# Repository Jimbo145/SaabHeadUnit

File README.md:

# SaabHeadUnit
The goal of this project is to create an alternate head unit option for the 
## saab-control

## circuit_boards

### headunit_controls

Emulates slimmed down ICM button pcb

### headunit_hub

Integrates Ibus and LCD connections to Cat V cables for routing out of ICM

### headunit_pi4

Pi4 mounting, Lifepowered, Microphone module, power input

# Project Phases

## Phase 1 -- ICM2 Integration

Parts list
[Raspberry Pi LCD 3.5inch touchscreen 480*800 capacitive](https://www.aliexpress.us/item/3256802078662650.html)
[lifepo4wered-pi+](https://lifepo4wered.com/lifepo4wered-pi+.html)
[Can Bus Module Mcp2515](https://www.aliexpress.us/item/3256802493611620.html)

## Phase 2 -- ICM Frontend Replacement

# Acknowledgement 

[leighleighleigh](https://github.com/leighleighleigh)
[Patrick Van Oosterwijck and LiFePO4wered](https://lifepo4wered.com)
[Trionic Tuning](https://www.trionictuning.com/forum/viewtopic.php?f=46&t=8566)

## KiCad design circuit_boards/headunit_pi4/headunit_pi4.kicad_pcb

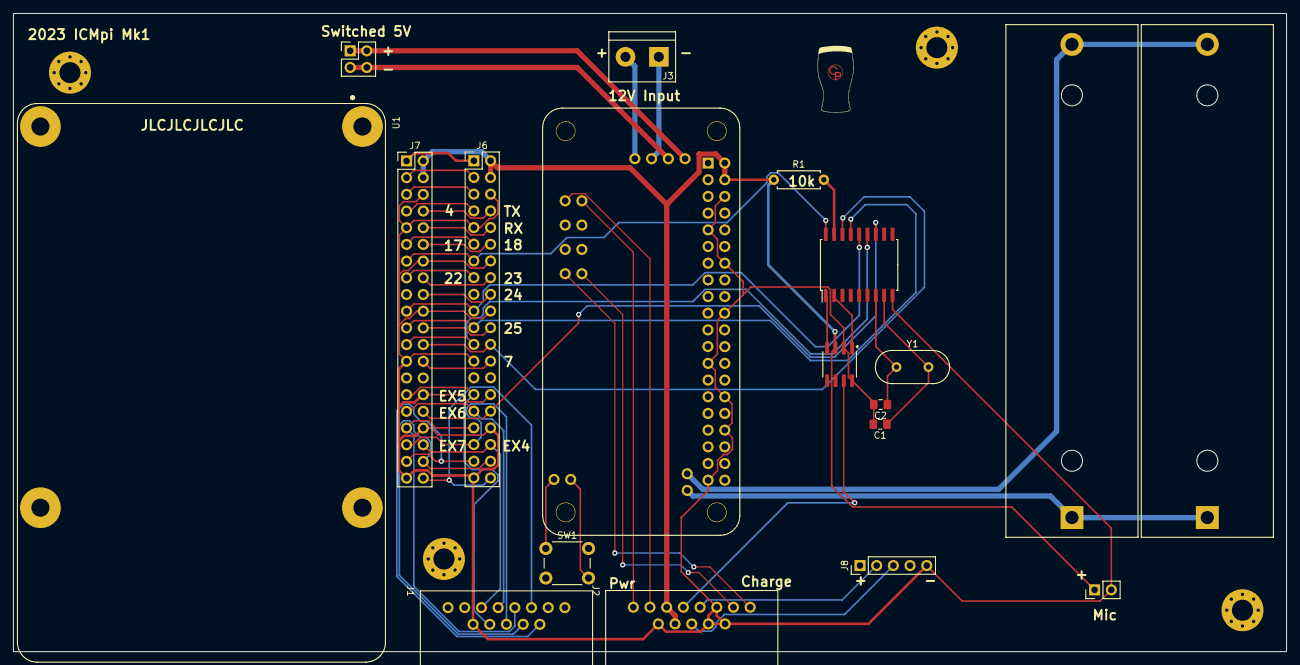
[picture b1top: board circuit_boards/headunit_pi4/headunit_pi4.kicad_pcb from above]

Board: 2 copper layers, 193.7 x 97.1 mm, 24 parts (0 on the bottom side), 50 nets.

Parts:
BT1, BT2: Battery_Cell; BatteryHolder_MPD_BH-18650-PC2
C1, C2: 22p; C_0805_2012Metric_Pad1.18x1.45mm_HandSolder
H1, H2, H3, H4: MountingHole_Pad; MountingHole_3.2mm_M3_Pad_Via
H5: MountingHole; CPlogo2(50)
J1, J2: 8P8C_LED_Shielded; rj45breakout
J3: Screw_Terminal_01x02; TerminalBlock_bornier-2_P5.08mm
J4: Conn_01x02; PinHeader_1x02_P2.54mm_Vertical
J5: Conn_02x02_Counter_Clockwise; PinHeader_2x02_P2.54mm_Vertical
J6, J7: Conn_02x20_Odd_Even; PinHeader_2x20_P2.54mm_Vertical
J8: USB_B_Mini; PinHeader_1x05_P2.54mm_Vertical
R1: 10k; R_Axial_DIN0207_L6.3mm_D2.5mm_P7.62mm_Horizontal
SW1: SW_Push; SW_PUSH_6mm
U1: RASPBERRY_PI_4B_4GB; MODULE_RASPBERRY_PI_4B_4GB_NOPIN
U2: TJA1051T; SOIC-8_3.9x4.9mm_P1.27mm
U3: MCP2515-xSO; SOIC-18W_7.5x11.6mm_P1.27mm
U4: LiFoPower
Y1: 8Mhz; Crystal_HC49-U_Vertical

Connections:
+3.3V: J6.1, J7.1
AMFM_button: J1.1, J6.37, J7.37
CAN_INT: J6.32, J7.32, U3.12 (~INT)
CD_button: J1.3, J6.38, J7.38
ChargeLED+: J2.10, U4.Cled+ (ChargeLED+)
ChargeLED-: J2.9, U4.Cled- (ChargeLED-)
Expansion_4: J1.8, J6.36, J7.36
Expansion_5: J1.7, J6.29, J7.29
Expansion_6: J1.6, J6.31, J7.31
Expansion_7: J1.5, J6.35, J7.35
GND: C1.2, C2.2, H1.1, H2.1, H3.1, H4.1, J1.SH, J2.1, J2.2, J2.3, J2.SH, J4.2, J6.6, J6.9, J6.14, J6.20, J6.25, J6.30, J6.34, J6.39, J7.6, J7.9, J7.14, J7.20, J7.25, J7.30, J7.34, J7.39, J8.5 (GND), U2.2 (GND), U2.8 (S), U3.9 (VSS), U4.6 (GND), U4.9 (GND), U4.14 (GND), U4.20 (GND), U4.25 (GND), U4.30 (GND), U4.34 (GND), U4.39 (GND)
GPIO4: J6.7, J7.7
GPIO7: J6.26, J7.26
GPIO17: J6.11, J7.11
GPIO18: J6.12, J7.12
GPIO22: J6.15, J7.15
GPIO23: J6.16, J7.16
GPIO24: J6.18, J7.18
GPIO25: J6.22, J7.22
LSCAN: J2.6, U2.7 (CANH)
MCP_PWR: J6.13, J7.13, U3.18 (VDD)
unnamed: BT1.1 (+), BT2.1 (+), U4.B+ (Bat+)
unnamed: BT1.2 (-), BT2.2 (-), U4.B- (Bat-)
unnamed: J3.1, U4.Vcar- (12VGND)
unnamed: J3.2, U4.Vcar+ (12V+)
unnamed: J5.1, J5.2, U4.Vout+
unnamed: J5.3, J5.4, U4.Vout-
unnamed: J2.5, J8.3 (D+)
unnamed: J2.4, J8.2 (D-)
unnamed: U1.S1 (SHIELD), U1.S2 (SHIELD), U1.S3 (SHIELD), U1.S4 (SHIELD)
unnamed: U2.4 (RXD), U3.2 (RXCAN)
unnamed: U2.1 (TXD), U3.1 (TXCAN)
unnamed: C1.1, U3.8 (OSC1), Y1.2
unnamed: C2.1, U3.7 (OSC2), Y1.1
unnamed: R1.2, U3.17 (~RESET)
unnamed: SW1.2, U4.btn+ (BTN+)
unnamed: SW1.1, U4.btn- (BTN-)
PwrLED+: J2.12, U4.Pled+ (PowerLED+)
PwrLED-: J2.11, U4.Pled- (PowerLED-)
RX0: J6.10, J7.10
SCAN_button: J1.2, J6.40, J7.40
SCL1: J6.5, J7.5, U4.5 (SCL)
SDA1: J6.3, J7.3, U4.3 (SDA)
SPI0_CE0: J6.24, J7.24, U3.16 (~CS)
SPI0_MISO: J6.21, J7.21, U3.15 (SO)
SPI0_MOSI: J6.19, J7.19, U3.14 (SI)
SPI0_SCLK: J6.23, J7.23, U3.13 (SCK)
Scrn_Brightness: J1.4, J6.33, J7.33
TX0: J6.8, J7.8, U4.8 (TX0)
VCC: J2.7, J2.8, J4.1, J6.2, J6.4, J7.2, J7.4, R1.1, U2.3 (VCC), U4.2 (VCC), U4.4 (VCC)

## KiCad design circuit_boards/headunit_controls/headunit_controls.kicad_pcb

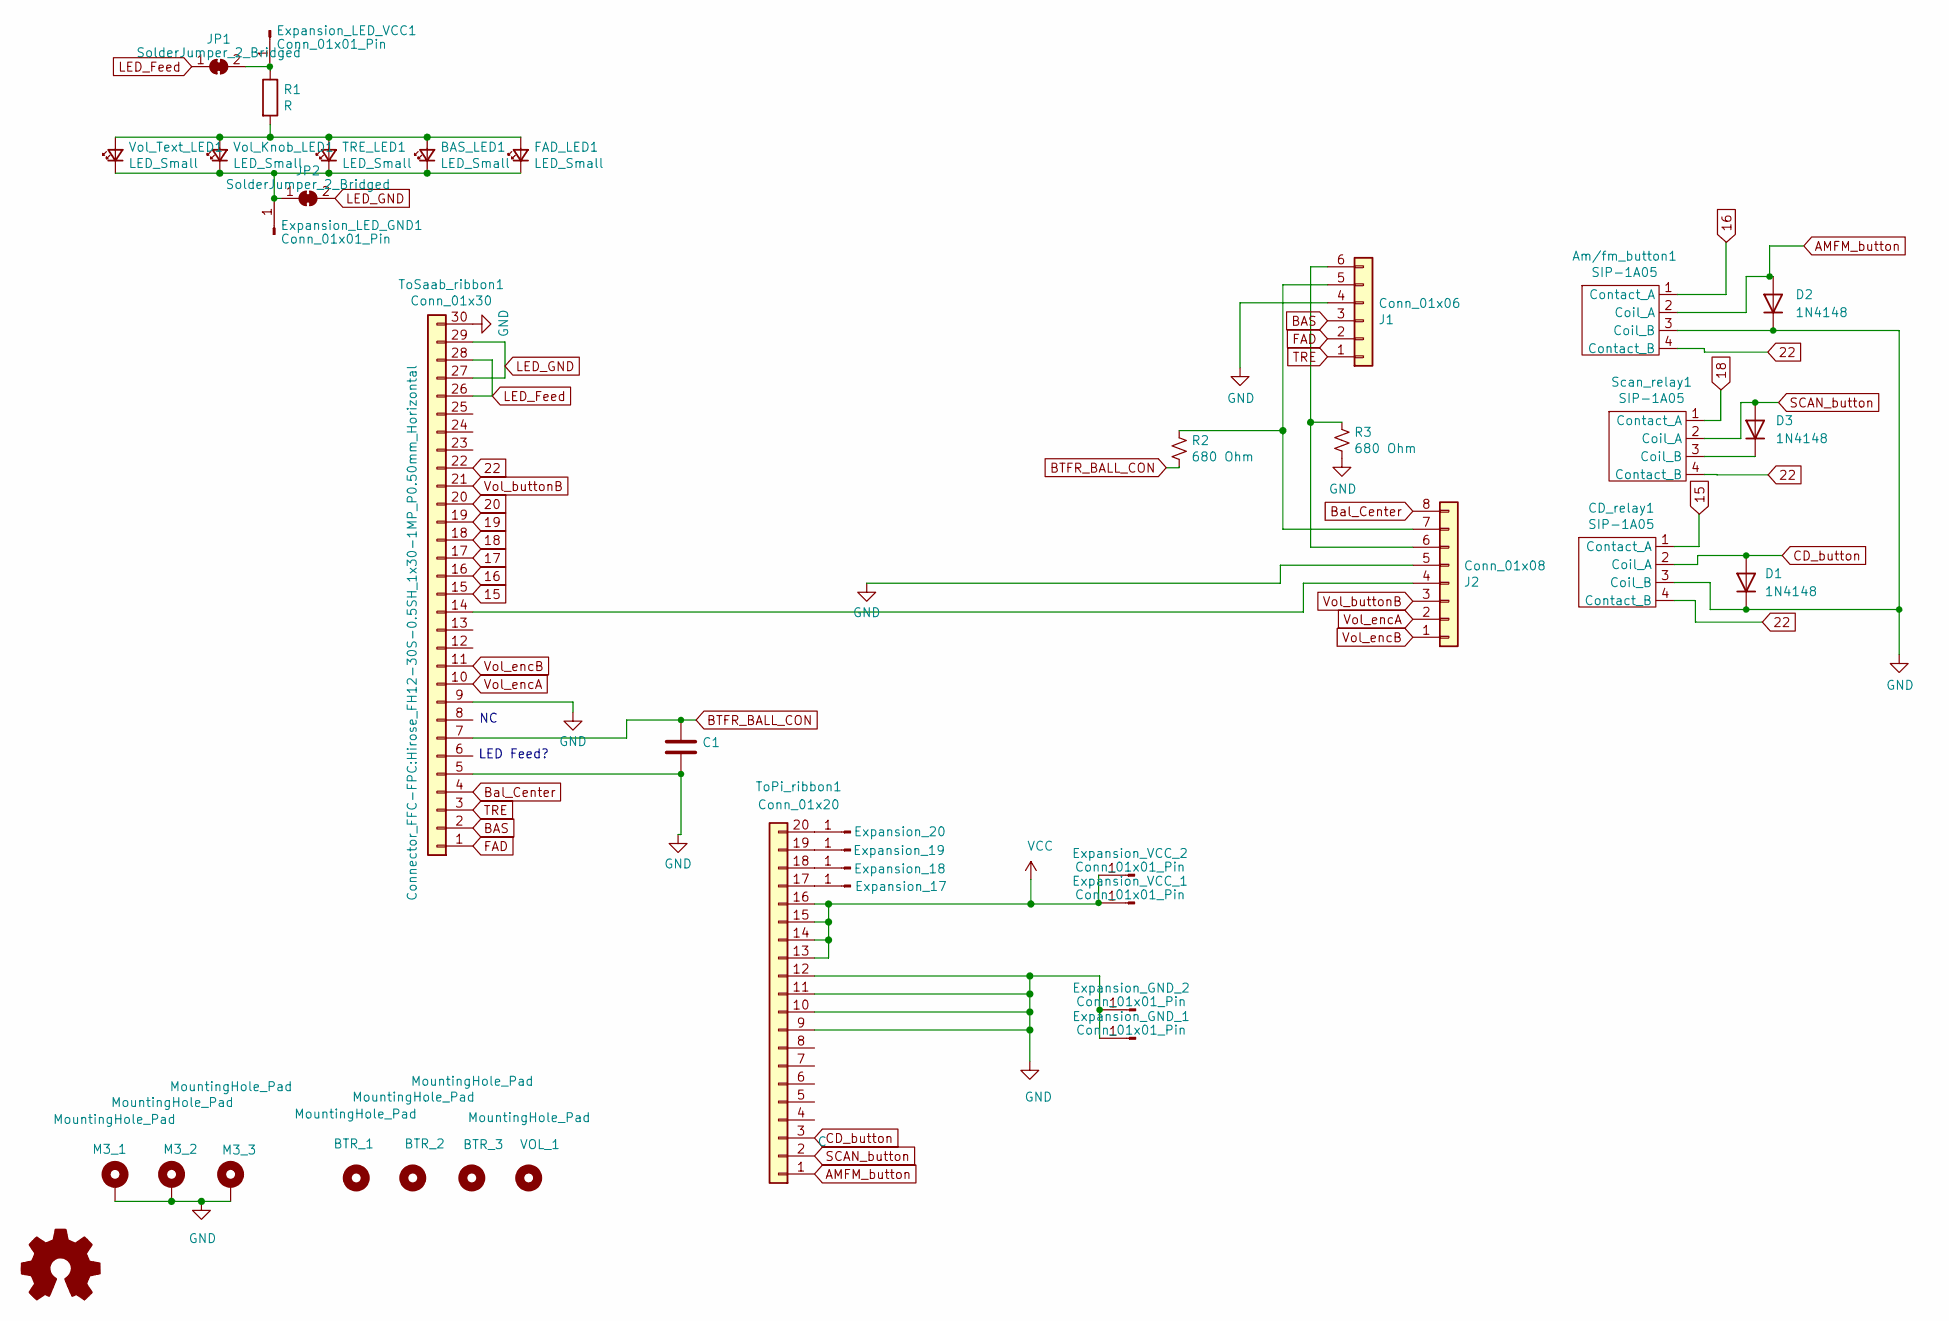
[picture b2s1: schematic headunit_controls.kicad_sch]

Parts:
Am/fm_button1: SIP-1A05; SIP1A05
BAS_LED1: LED_Small; LED_OF-SMD3528WC
BTR_1, BTR_2, BTR_3: MountingHole_Pad; SaabBTR
C1: C; C_0805_2012Metric_Pad1.18x1.45mm_HandSolder
CD_relay1: SIP-1A05; SIP1A05
D1, D2, D3: 1N4148; D_DO-35_SOD27_P7.62mm_Horizontal
Expansion_17, Expansion_18, Expansion_19, Expansion_20: Conn_01x01_Pin; TestPoint_Pad_2.0x2.0mm
Expansion_GND_1, Expansion_GND_2: Conn_01x01_Pin; TestPoint_Pad_2.0x2.0mm
Expansion_LED_GND1: Conn_01x01_Pin; TestPoint_Pad_2.0x2.0mm
Expansion_LED_VCC1: Conn_01x01_Pin; TestPoint_Pad_2.0x2.0mm
Expansion_VCC_1, Expansion_VCC_2: Conn_01x01_Pin; TestPoint_Pad_2.0x2.0mm
FAD_LED1: LED_Small; LED_OF-SMD3528WC
J1: Conn_01x06; SaabConnector_6
J2: Conn_01x08; SaabConnector_8
JP1, JP2: SolderJumper_2_Bridged; SolderJumper-2_P1.3mm_Bridged2Bar_Pad1.0x1.5mm
M3_1, M3_2, M3_3: MountingHole_Pad; MountingHole_3.2mm_M3_Pad
R1: R; R_0603_1608Metric_Pad0.98x0.95mm_HandSolder
R2, R3: 680 Ohm; R_0603_1608Metric_Pad0.98x0.95mm_HandSolder
Scan_relay1: SIP-1A05; SIP1A05
TRE_LED1: LED_Small; LED_OF-SMD3528WC
ToPi_ribbon1: Conn_01x20; Hirose_FH12-20S-0.5SH_1x20-1MP_P0.50mm_Horizontal
ToSaab_ribbon1: Conn_01x30; Hirose_FH12-30S-0.5SH_1x30-1MP_P0.50mm_Horizontal
VOL_1: MountingHole_Pad; SaabBTR
Vol_Knob_LED1: LED_Small; Songxin_1210_side
Vol_Text_LED1: LED_Small; LED_OF-SMD3528WC

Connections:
15: CD_relay1.1 (Contact_A), ToSaab_ribbon1.15
16: Am/fm_button1.1 (Contact_A), ToSaab_ribbon1.16
17: ToSaab_ribbon1.17
18: Scan_relay1.1 (Contact_A), ToSaab_ribbon1.18
19: ToSaab_ribbon1.19
20: ToSaab_ribbon1.20
22: Am/fm_button1.4 (Contact_B), CD_relay1.4 (Contact_B), Scan_relay1.4 (Contact_B), ToSaab_ribbon1.22
AMFM_button: Am/fm_button1.2 (Coil_A), D2.2 (A), ToPi_ribbon1.1
BAS: J1.3, ToSaab_ribbon1.2
BTFR_BALL_CON: C1.1, R2.2, ToSaab_ribbon1.7
Bal_Center: J2.8, ToSaab_ribbon1.4
CD_button: CD_relay1.2 (Coil_A), D1.2 (A), ToPi_ribbon1.3
FAD: J1.2, ToSaab_ribbon1.1
GND: Am/fm_button1.3 (Coil_B), C1.2, CD_relay1.3 (Coil_B), D1.1 (K), D2.1 (K), Expansion_GND_1.1, Expansion_GND_2.1, J1.4, J2.5, M3_1.1, M3_2.1, M3_3.1, R3.2, ToPi_ribbon1.9, ToPi_ribbon1.10, ToPi_ribbon1.11, ToPi_ribbon1.12, ToSaab_ribbon1.5, ToSaab_ribbon1.9, ToSaab_ribbon1.30; also elsewhere on the board
LED_Feed: JP1.1 (A), ToSaab_ribbon1.26, ToSaab_ribbon1.28
LED_GND: JP2.2 (B), ToSaab_ribbon1.27, ToSaab_ribbon1.29
unnamed: BAS_LED1.2 (A), FAD_LED1.2 (A), R1.2, TRE_LED1.2 (A), Vol_Knob_LED1.2 (A), Vol_Text_LED1.2 (A)
unnamed: BAS_LED1.1 (K), Expansion_LED_GND1.1, FAD_LED1.1 (K), JP2.1 (A), TRE_LED1.1 (K), Vol_Knob_LED1.1 (K), Vol_Text_LED1.1 (K)
unnamed: D3.1 (K), Scan_relay1.3 (Coil_B)
unnamed: Expansion_17.1, ToPi_ribbon1.17
unnamed: Expansion_18.1, ToPi_ribbon1.18
unnamed: Expansion_19.1, ToPi_ribbon1.19
unnamed: Expansion_20.1, ToPi_ribbon1.20
unnamed: Expansion_LED_VCC1.1, JP1.2 (B), R1.1
unnamed: J1.5, J2.7, R2.1
unnamed: J1.6, J2.6, R3.1
unnamed: J2.4, ToSaab_ribbon1.14
SCAN_button: D3.2 (A), Scan_relay1.2 (Coil_A), ToPi_ribbon1.2
TRE: J1.1, ToSaab_ribbon1.3
VCC: Expansion_VCC_1.1, Expansion_VCC_2.1, ToPi_ribbon1.13, ToPi_ribbon1.14, ToPi_ribbon1.15, ToPi_ribbon1.16
Vol_buttonB: J2.3, ToSaab_ribbon1.21
Vol_encA: J2.2, ToSaab_ribbon1.10
Vol_encB: J2.1, ToSaab_ribbon1.11

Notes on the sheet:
LED Feed?

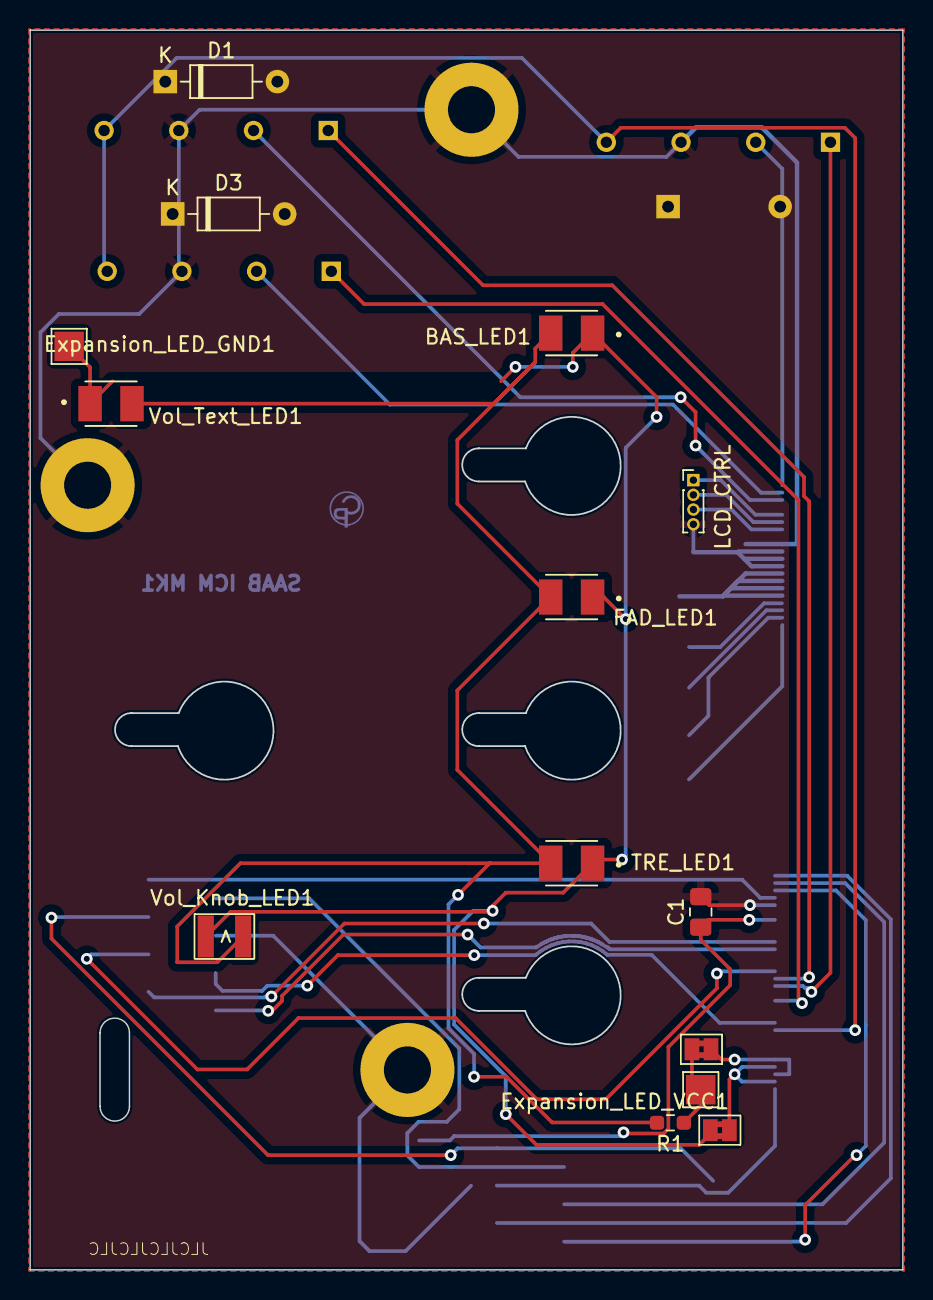
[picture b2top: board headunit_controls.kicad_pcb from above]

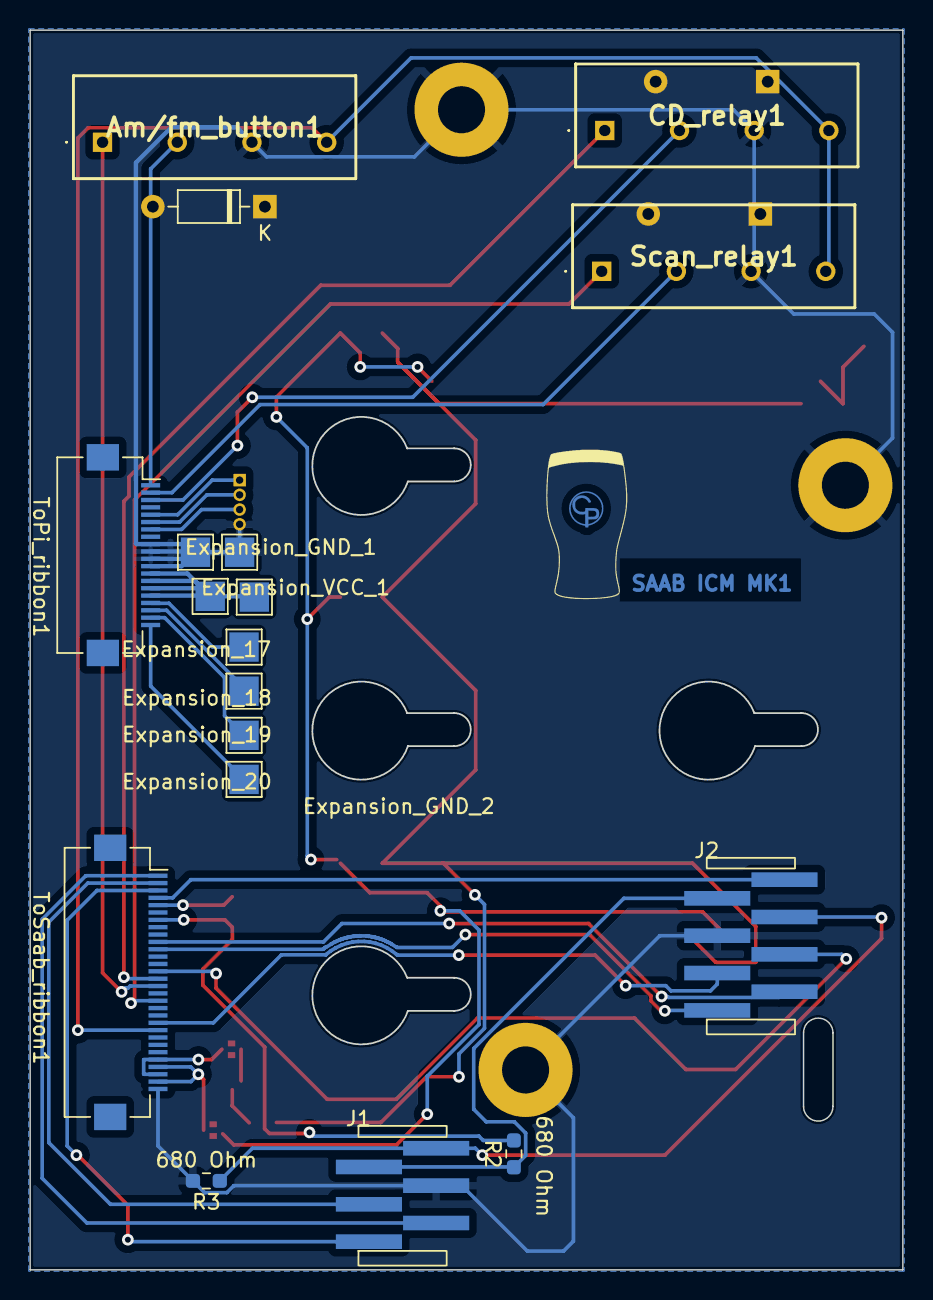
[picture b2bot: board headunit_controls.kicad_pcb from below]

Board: 2 copper layers, 59.3 x 84.3 mm, 40 parts (19 on the bottom side), 30 nets.

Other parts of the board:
LCD_CTRL: Conn_01x04_Pin; PinHeader_1x04_P1.00mm_Vertical
Ref**: Val**; CPlogo2(50)

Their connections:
GND: LCD_CTRL.4; also elsewhere on the board

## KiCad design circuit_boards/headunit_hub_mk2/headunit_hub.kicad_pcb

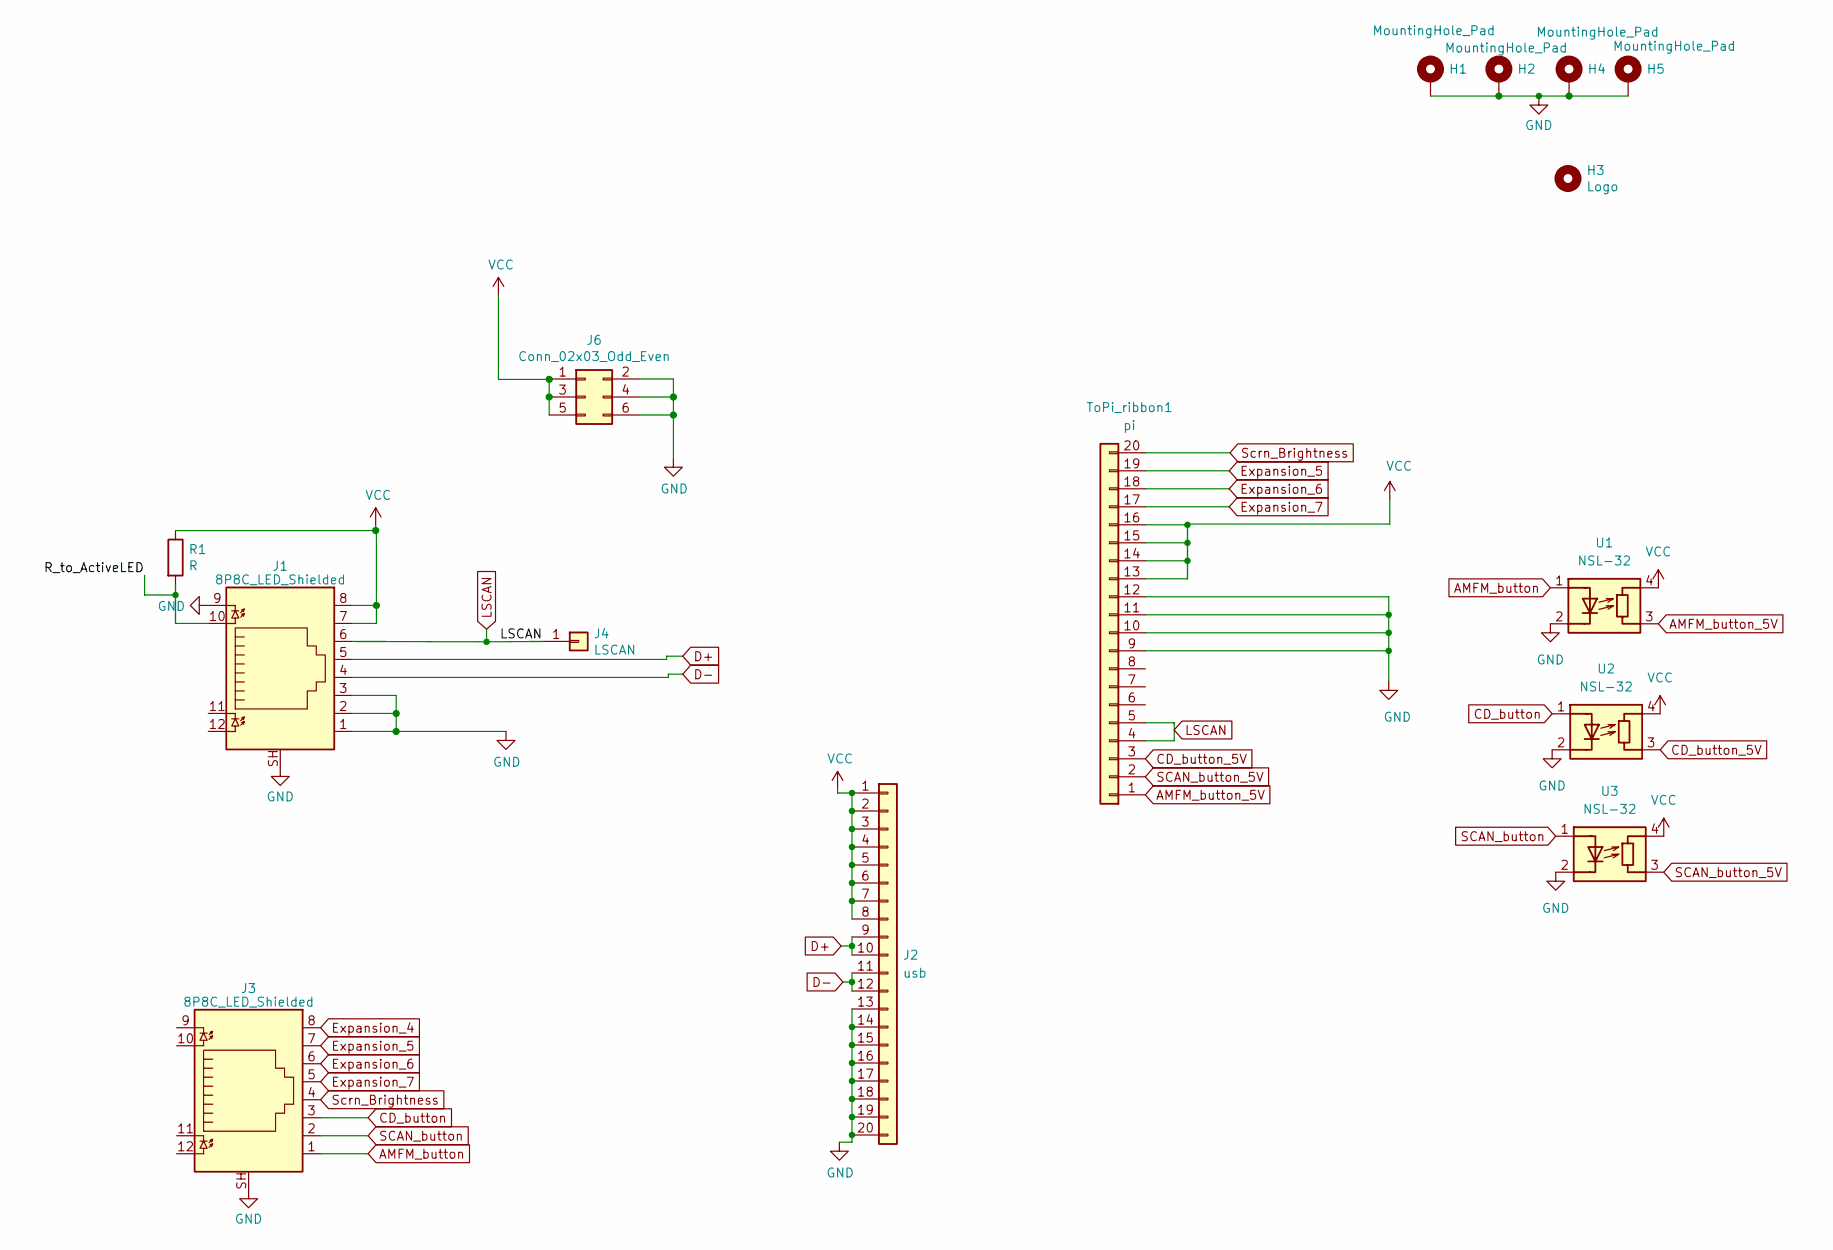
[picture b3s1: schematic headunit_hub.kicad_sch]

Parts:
H1, H2, H4, H5: MountingHole_Pad; MountingHole_3.2mm_M3_Pad_Via
H3: Logo; CPlogo2(50)
J1, J3: 8P8C_LED_Shielded; RJ45_Amphenol_RJHSE538X
J2: usb; Hirose_FH12-20S-0.5SH_1x20-1MP_P0.50mm_Horizontal
J4: LSCAN; PinHeader_1x01_P2.54mm_Vertical
J6: Conn_02x03_Odd_Even; PinHeader_2x03_P2.54mm_Vertical
R1: R; R_Axial_DIN0207_L6.3mm_D2.5mm_P10.16mm_Horizontal
ToPi_ribbon1: pi; Hirose_FH12-20S-0.5SH_1x20-1MP_P0.50mm_Horizontal
U1, U2, U3: NSL-32; Luna_NSL-32

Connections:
/R_to_ActiveLED: J1.10, R1.2
AMFM_button: J3.1, U1.1 (A)
AMFM_button_5V: ToPi_ribbon1.1, U1.3 (R)
CD_button: J3.3, U2.1 (A)
CD_button_5V: ToPi_ribbon1.3, U2.3 (R)
D+: J1.5, J2.9, J2.10
D-: J1.4, J2.11, J2.12
Expansion_4: J3.8
Expansion_5: J3.7, ToPi_ribbon1.19
Expansion_6: J3.6, ToPi_ribbon1.18
Expansion_7: J3.5, ToPi_ribbon1.17
GND: H1.1, H2.1, H4.1, H5.1, J1.1, J1.2, J1.3, J1.9, J1.SH, J2.13, J2.14, J2.15, J2.16, J2.17, J2.18, J2.19, J2.20, J3.SH, J6.2, J6.4, J6.6, ToPi_ribbon1.9, ToPi_ribbon1.10, ToPi_ribbon1.11, ToPi_ribbon1.12, U1.2 (K), U2.2 (K), U3.2 (K)
LSCAN: J1.6, J4.1, ToPi_ribbon1.4, ToPi_ribbon1.5
SCAN_button: J3.2, U3.1 (A)
SCAN_button_5V: ToPi_ribbon1.2, U3.3 (R)
Scrn_Brightness: J3.4, ToPi_ribbon1.20
VCC: J1.7, J1.8, J2.1, J2.2, J2.3, J2.4, J2.5, J2.6, J2.7, J2.8, J6.1, J6.3, J6.5, R1.1, ToPi_ribbon1.13, ToPi_ribbon1.14, ToPi_ribbon1.15, ToPi_ribbon1.16, U1.4 (R), U2.4 (R), U3.4 (R)

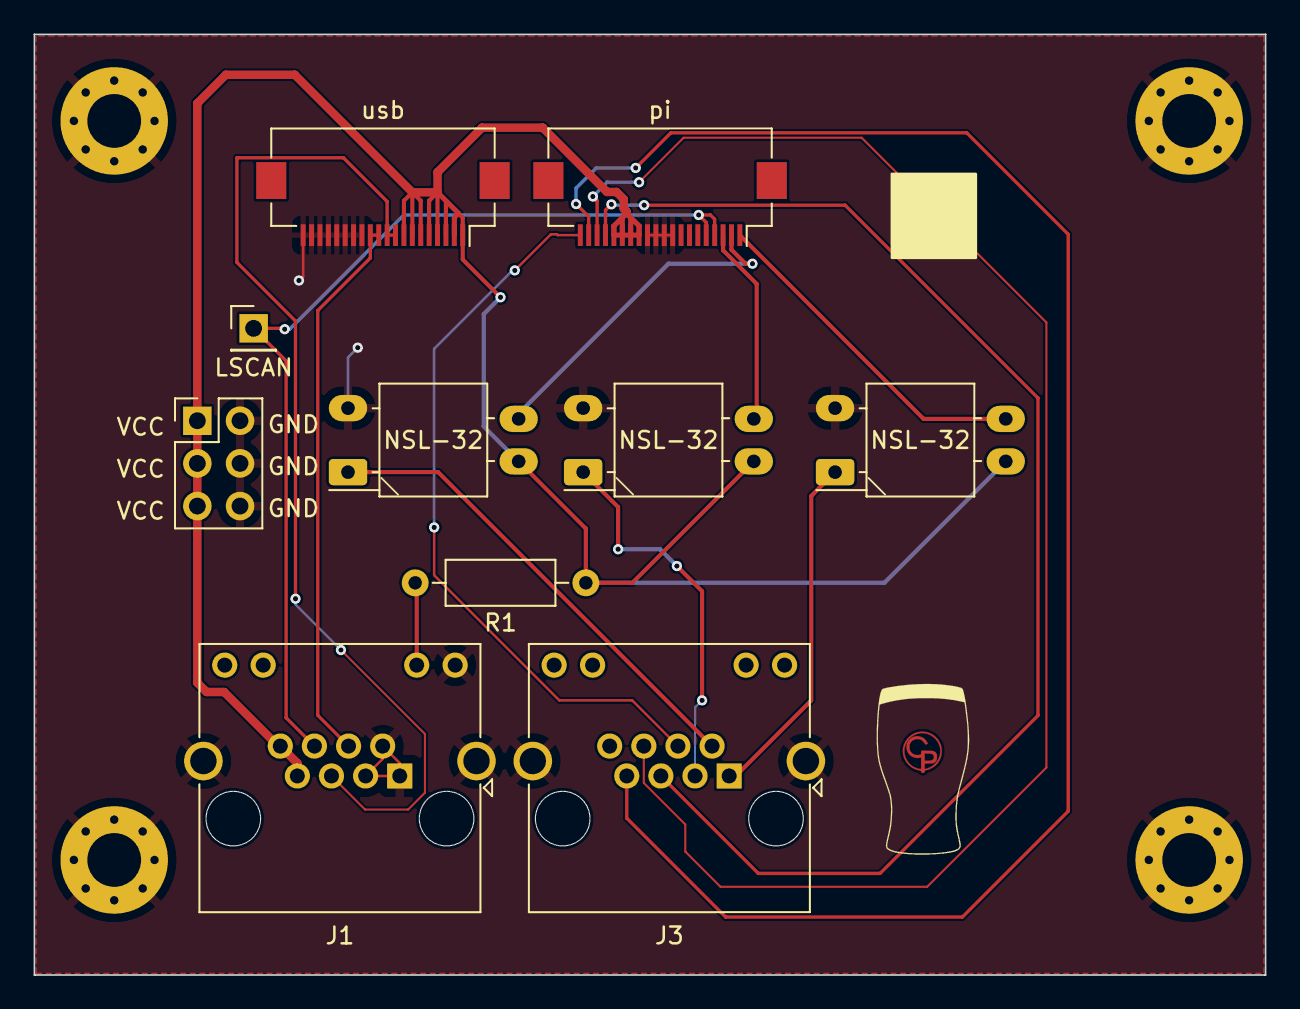
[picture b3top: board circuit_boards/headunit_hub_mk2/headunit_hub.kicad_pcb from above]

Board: 2 copper layers, 73.3 x 56.0 mm, 15 parts (0 on the bottom side), 16 nets.

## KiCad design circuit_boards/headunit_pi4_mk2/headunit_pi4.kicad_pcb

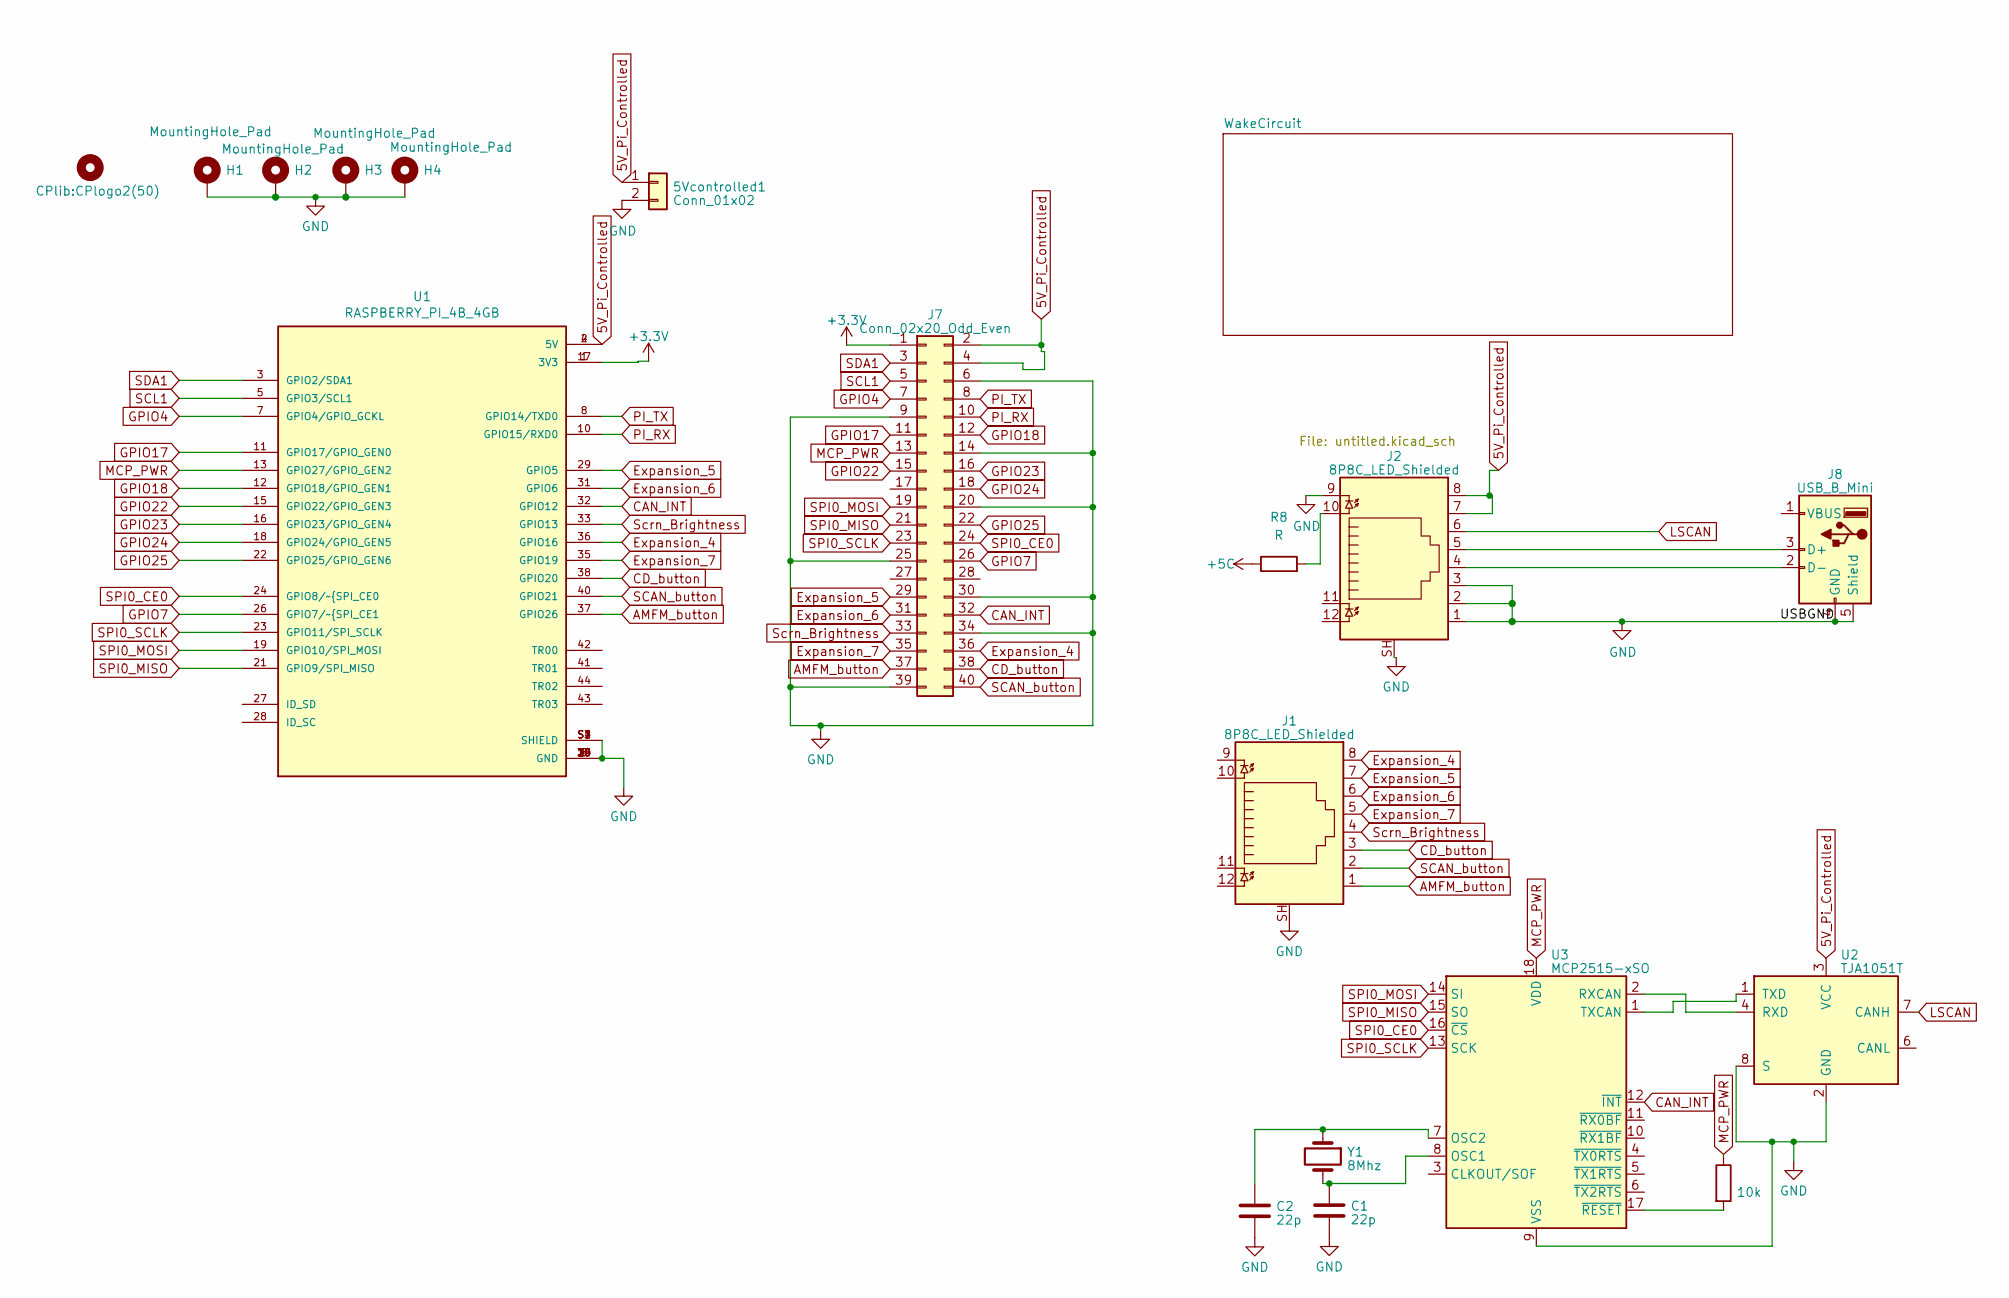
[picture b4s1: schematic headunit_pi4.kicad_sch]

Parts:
5Vcontrolled1: Conn_01x02; PinHeader_1x02_P2.54mm_Vertical
C1, C2: 22p; C_0805_2012Metric_Pad1.18x1.45mm_HandSolder
H1, H2, H3, H4: MountingHole_Pad; MountingHole_3.2mm_M3_Pad_Via
H5: MountingHole; CPlogo2(50)
J1, J2: 8P8C_LED_Shielded; RJ45_Amphenol_RJHSE538X
J7: Conn_02x20_Odd_Even; PinHeader_2x20_P2.54mm_Vertical
J8: USB_B_Mini; USB_A_Molex_67643_Horizontal
R1: 10k; R_Axial_DIN0207_L6.3mm_D2.5mm_P10.16mm_Horizontal
R8: R; R_Axial_DIN0207_L6.3mm_D2.5mm_P10.16mm_Horizontal
U1: RASPBERRY_PI_4B_4GB; MODULE_RASPBERRY_PI_4B_4GB; PARTREV 4
U2: TJA1051T; SOIC-8_3.9x4.9mm_P1.27mm
U3: MCP2515-xSO; SOIC-18W_7.5x11.6mm_P1.27mm
Y1: 8Mhz; Crystal_HC49-U_Vertical

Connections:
5V_Pi_Controlled: 5Vcontrolled1.1, J2.7, J2.8, J7.2, J7.4, U1.2 (5V), U1.4 (5V), U2.3 (VCC); also elsewhere on the board
+3.3V: J7.1, U1.1 (3V3), U1.17 (3V3)
+5C: R8.1; also elsewhere on the board
AMFM_button: J1.1, J7.37, U1.37 (GPIO26)
CAN_INT: J7.32, U1.32 (GPIO12), U3.12 (~INT)
CD_button: J1.3, J7.38, U1.38 (GPIO20)
Expansion_4: J1.8, J7.36, U1.36 (GPIO16)
Expansion_5: J1.7, J7.29, U1.29 (GPIO5)
Expansion_6: J1.6, J7.31, U1.31 (GPIO6)
Expansion_7: J1.5, J7.35, U1.35 (GPIO19)
GND: 5Vcontrolled1.2, C1.2, C2.2, H1.1, H2.1, H3.1, H4.1, J1.SH, J2.1, J2.2, J2.3, J2.9, J2.SH, J7.6, J7.9, J7.14, J7.20, J7.25, J7.30, J7.34, J7.39, J8.4 (GND), J8.5 (Shield), U1.6 (GND), U1.9 (GND), U1.14 (GND), U1.20 (GND), U1.25 (GND), U1.30 (GND), U1.34 (GND), U1.39 (GND), U1.S1 (SHIELD), U1.S2 (SHIELD), U1.S3 (SHIELD), U1.S4 (SHIELD), U2.2 (GND), U2.8 (S), U3.9 (VSS); also elsewhere on the board
GPIO4: J7.7, U1.7 (GPIO4/GPIO_GCKL)
GPIO7: J7.26, U1.26 (GPIO7/~SPI_CE1~{)
GPIO17: J7.11, U1.11 (GPIO17/GPIO_GEN0)
GPIO18: J7.12, U1.12 (GPIO18/GPIO_GEN1)
GPIO22: J7.15, U1.15 (GPIO22/GPIO_GEN3)
GPIO23: J7.16, U1.16 (GPIO23/GPIO_GEN4)
GPIO24: J7.18, U1.18 (GPIO24/GPIO_GEN5)
GPIO25: J7.22, U1.22 (GPIO25/GPIO_GEN6)
LSCAN: J2.6, U2.7 (CANH); also elsewhere on the board
MCP_PWR: J7.13, R1.1, U1.13 (GPIO27/GPIO_GEN2), U3.18 (VDD)
unnamed: J2.10, R8.2
unnamed: J2.5, J8.3 (D+)
unnamed: J2.4, J8.2 (D-)
unnamed: U2.4 (RXD), U3.2 (RXCAN)
unnamed: U2.1 (TXD), U3.1 (TXCAN)
unnamed: C1.1, U3.8 (OSC1), Y1.2
unnamed: C2.1, U3.7 (OSC2), Y1.1
unnamed: R1.2, U3.17 (~RESET)
PI_RX: J7.10, U1.10 (GPIO15/RXD0); also elsewhere on the board
PI_TX: J7.8, U1.8 (GPIO14/TXD0); also elsewhere on the board
SCAN_button: J1.2, J7.40, U1.40 (GPIO21)
SCL1: J7.5, U1.5 (GPIO3/SCL1)
SDA1: J7.3, U1.3 (GPIO2/SDA1)
SPI0_CE0: J7.24, U1.24 (GPIO8/~SPI_CE0~{), U3.16 (~CS)
SPI0_MISO: J7.21, U1.21 (GPIO9/SPI_MISO), U3.15 (SO)
SPI0_MOSI: J7.19, U1.19 (GPIO10/SPI_MOSI), U3.14 (SI)
SPI0_SCLK: J7.23, U1.23 (GPIO11/SPI_SCLK), U3.13 (SCK)
Scrn_Brightness: J1.4, J7.33, U1.33 (GPIO13)

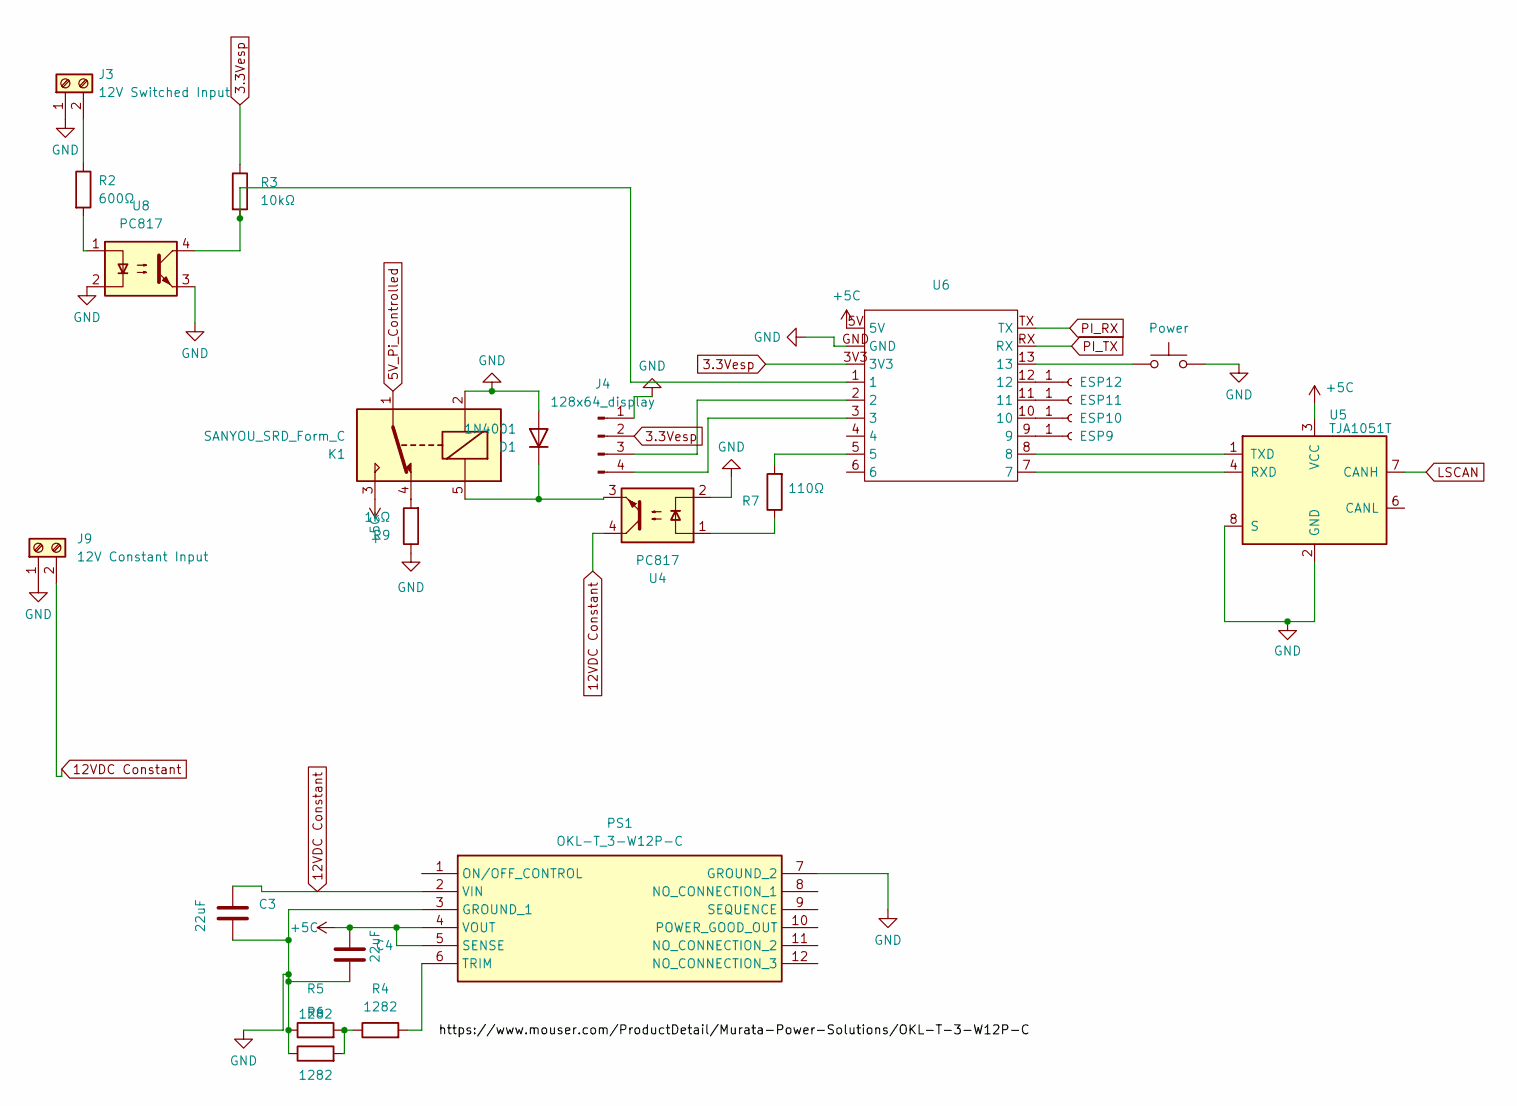
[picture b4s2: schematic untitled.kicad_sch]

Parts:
C3, C4: 22uF; C_0805_2012Metric_Pad1.18x1.45mm_HandSolder
D1: 1N4001; D_DO-41_SOD81_P10.16mm_Horizontal
J3: 12V Switched Input; TerminalBlock_bornier-2_P5.08mm
J4: 128x64_display; 128x64
J5: ESP11; TestPoint_Pad_2.0x2.0mm
J6: ESP12; TestPoint_Pad_2.0x2.0mm
J9: 12V Constant Input; TerminalBlock_bornier-2_P5.08mm
J10: ESP9; TestPoint_Pad_2.0x2.0mm
J11: ESP10; TestPoint_Pad_2.0x2.0mm
K1: SANYOU_SRD_Form_C; Relay_SPDT_SANYOU_SRD_Series_Form_C
PS1: OKL-T_3-W12P-C; OKLT3W12PC; Manufacturer_Part_Number OKL-T/3-W12P-C
Power: Power; SW_PUSH_6mm_H4.3mm
R2: 600Ω; R_Axial_DIN0207_L6.3mm_D2.5mm_P10.16mm_Horizontal
R3: 10kΩ; R_Axial_DIN0207_L6.3mm_D2.5mm_P10.16mm_Horizontal
R4, R5, R6: 1282; R_Axial_DIN0207_L6.3mm_D2.5mm_P10.16mm_Horizontal
R7: 110Ω; R_Axial_DIN0207_L6.3mm_D2.5mm_P10.16mm_Horizontal
R9: 1kΩ; R_Axial_DIN0207_L6.3mm_D2.5mm_P10.16mm_Horizontal
U4, U8: PC817; DIP-4_W7.62mm
U5: TJA1051T; SOIC-8_3.9x4.9mm_P1.27mm
U6: ESP32-S3-Zero

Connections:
3.3Vesp: J4.2 (VDD), R3.1, U6.3V3
5V_Pi_Controlled: K1.1; also elsewhere on the board
12VDC Constant: C3.1, J9.2, PS1.2 (VIN), U4.4
+5C: C4.1, K1.3, PS1.4 (VOUT), PS1.5 (SENSE), U5.3 (VCC), U6.5V; also elsewhere on the board
GND: C3.2, C4.2, D1.2 (A), J3.1, J4.1 (GND), J9.1, K1.2, PS1.3 (GROUND_1), PS1.7 (GROUND_2), Power.2, R5.1, R6.1, R9.1, U4.2, U5.2 (GND), U5.8 (S), U6.GND, U8.2, U8.3; also elsewhere on the board
LSCAN: U5.7 (CANH); also elsewhere on the board
unnamed: D1.1 (K), K1.5, U4.3
unnamed: J3.2, R2.1
unnamed: J4.3 (SCK), U6.2
unnamed: J4.4 (SDA), U6.3
unnamed: J5.1, U6.11
unnamed: J6.1, U6.12
unnamed: J10.1, U6.9
unnamed: J11.1, U6.10
unnamed: K1.4, R9.2
unnamed: PS1.6 (TRIM), R4.2
unnamed: R2.2, U8.1
unnamed: R3.2, U6.1, U8.4
unnamed: R4.1, R5.2, R6.2
unnamed: R7.1, U4.1
unnamed: R7.2, U6.5
unnamed 41: Power.1, U6.13; also elsewhere on the board
unnamed: U5.4 (RXD), U6.7
unnamed: U5.1 (TXD), U6.8
PI_RX: U6.TX; also elsewhere on the board
PI_TX: U6.RX; also elsewhere on the board

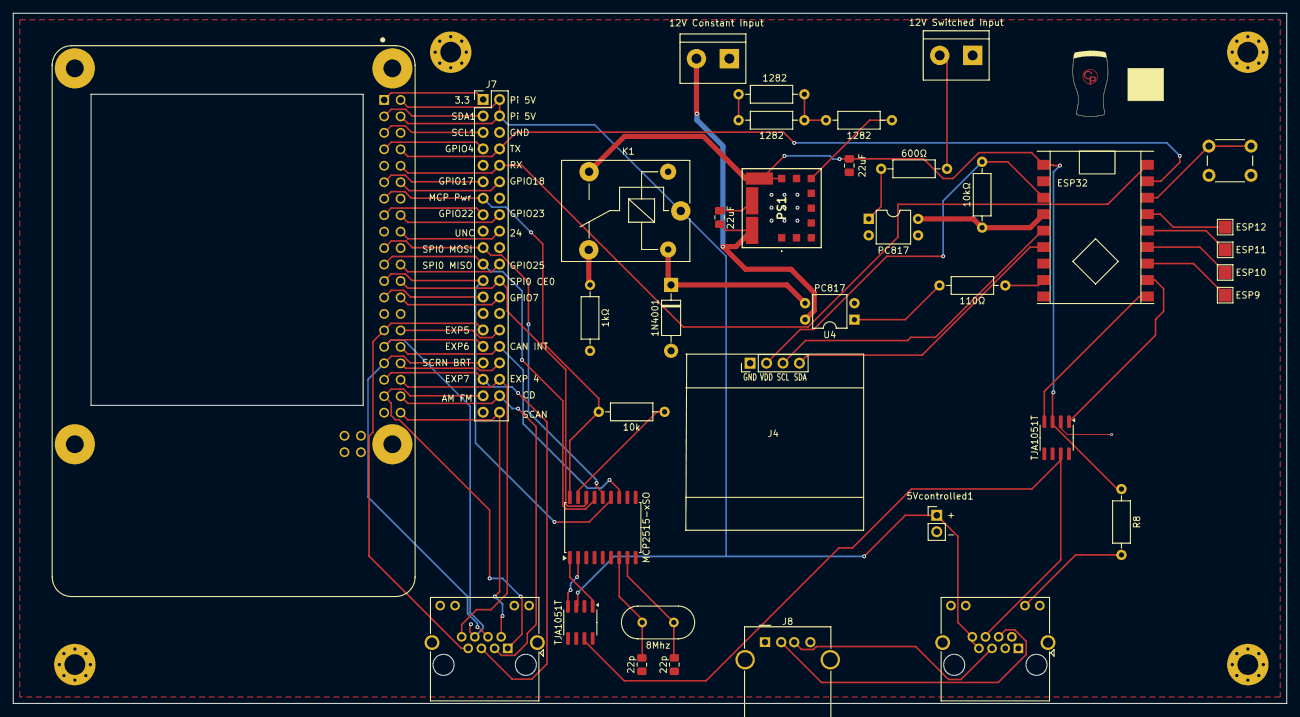
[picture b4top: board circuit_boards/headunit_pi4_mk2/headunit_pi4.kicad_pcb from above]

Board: 2 copper layers, 196.5 x 106.5 mm, 42 parts (0 on the bottom side), 59 nets.

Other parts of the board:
SW1: Power; SW_PUSH_6mm_H4.3mm

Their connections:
GND: SW1.2; also elsewhere on the board
unnamed 41: SW1.1; also elsewhere on the board
